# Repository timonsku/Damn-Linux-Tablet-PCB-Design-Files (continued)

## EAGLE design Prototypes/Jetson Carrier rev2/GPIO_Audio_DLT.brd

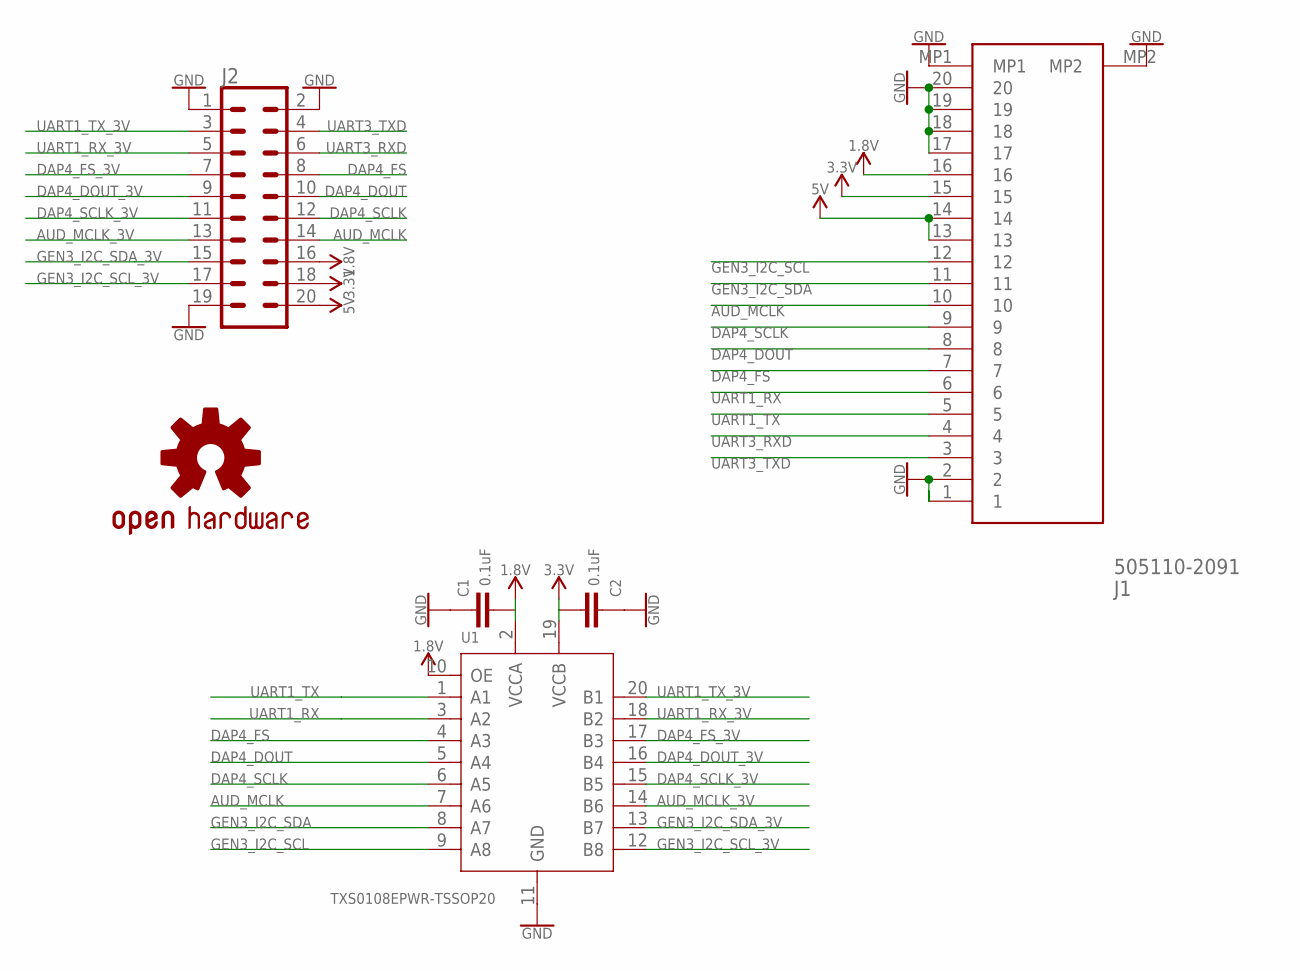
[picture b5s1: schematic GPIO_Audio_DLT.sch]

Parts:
C1, C2: 0.1uF; 0603
J1: 505110-2091; 5051102091
J2: CONN_10X2; 2X10
LOGO1: OSHW-LOGOS-COPPER; OSHW-LOGO-S_COPPER
U1: TXS0108EPWR-TSSOP20; TSSOP20-0.65-6.5X4.4MM

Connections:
1.8V: C1.2, J1.16, J2.16, U1.2 (VCCA), U1.10 (OE)
3.3V: C2.1, J1.15, J2.18, U1.19 (VCCB)
5V: J1.13, J1.14, J2.20
AUD_MCLK: J1.10, J2.14, U1.7 (A6)
AUD_MCLK_3V: J2.13, U1.14 (B6)
DAP4_DOUT: J1.8, J2.10, U1.5 (A4)
DAP4_DOUT_3V: J2.9, U1.16 (B4)
DAP4_FS: J1.7, J2.8, U1.4 (A3)
DAP4_FS_3V: J2.7, U1.17 (B3)
DAP4_SCLK: J1.9, J2.12, U1.6 (A5)
DAP4_SCLK_3V: J2.11, U1.15 (B5)
GEN3_I2C_SCL: J1.12, U1.9 (A8)
GEN3_I2C_SCL_3V: J2.17, U1.12 (B8)
GEN3_I2C_SDA: J1.11, U1.8 (A7)
GEN3_I2C_SDA_3V: J2.15, U1.13 (B7)
GND: C1.1, C2.2, J1.1, J1.2, J1.17, J1.18, J1.19, J1.20, J1.MP1, J1.MP2, J2.1, J2.2, J2.19, U1.11 (GND)
UART1_RX: J1.6, U1.3 (A2)
UART1_RX_3V: J2.5, U1.18 (B2)
UART1_TX: J1.5, U1.1 (A1)
UART1_TX_3V: J2.3, U1.20 (B1)
UART3_RXD: J1.4, J2.6
UART3_TXD: J1.3, J2.4

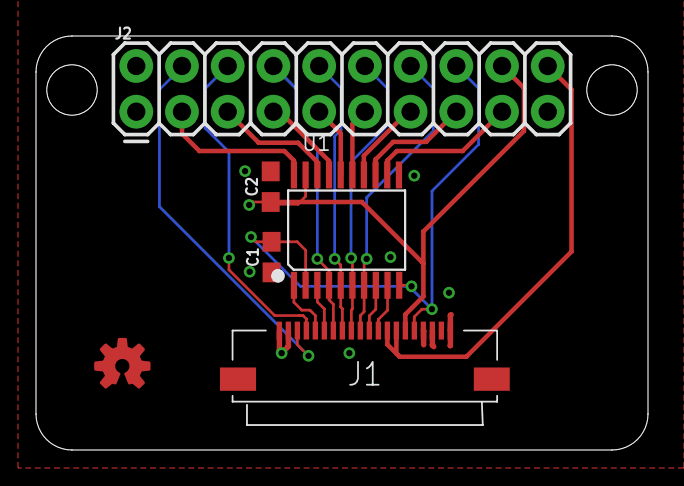
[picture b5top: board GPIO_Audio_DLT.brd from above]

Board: 2 copper layers, 34.0 x 23.0 mm, 6 parts (0 on the bottom side), 22 nets.

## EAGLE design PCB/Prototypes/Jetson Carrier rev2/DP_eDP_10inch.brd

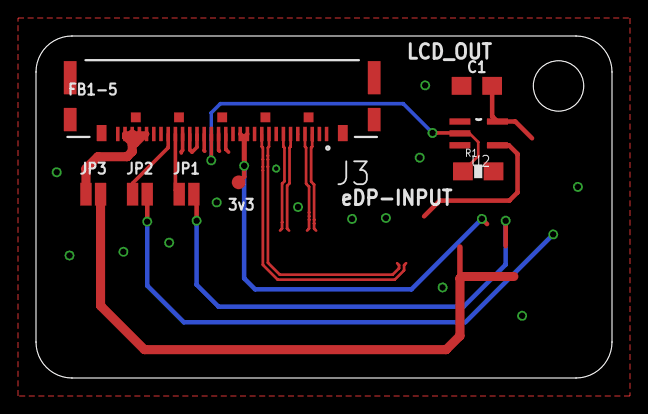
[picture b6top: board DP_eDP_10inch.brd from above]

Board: 4 copper layers, 32.0 x 19.0 mm, 8 parts (0 on the bottom side), 7 nets.

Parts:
C1: 0.1uF; 0603
J3: 20525-030E-2; I-PEX_20525-030E-2
JP1, JP2, JP3: JUMPER-SMT_2_NC_PASTE_NO-SILK; SMT-JUMPER_2_NC_PASTE_NO-SILK
R1: 100k; 0603-RES
TP7: TEST-POINT3; PAD.03X.03
U2: SN74LV1T125DCKR; SOT65P210X110-5N

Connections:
1.8V: C1.2, U2.5
DP_HPD_IN: J3.17, R1.1, U2.2
DP_PWR_3V3: J3.12, J3.13, TP7.P$1
GND: C1.1, J3.2, J3.5, J3.8, J3.11, J3.15, J3.16, J3.18, J3.19, J3.20, J3.21, R1.2, U2.1, U2.3
unnamed: J3.22, JP1.1
unnamed: J3.23, JP2.1
unnamed: J3.26, J3.27, J3.28, J3.29, JP3.1

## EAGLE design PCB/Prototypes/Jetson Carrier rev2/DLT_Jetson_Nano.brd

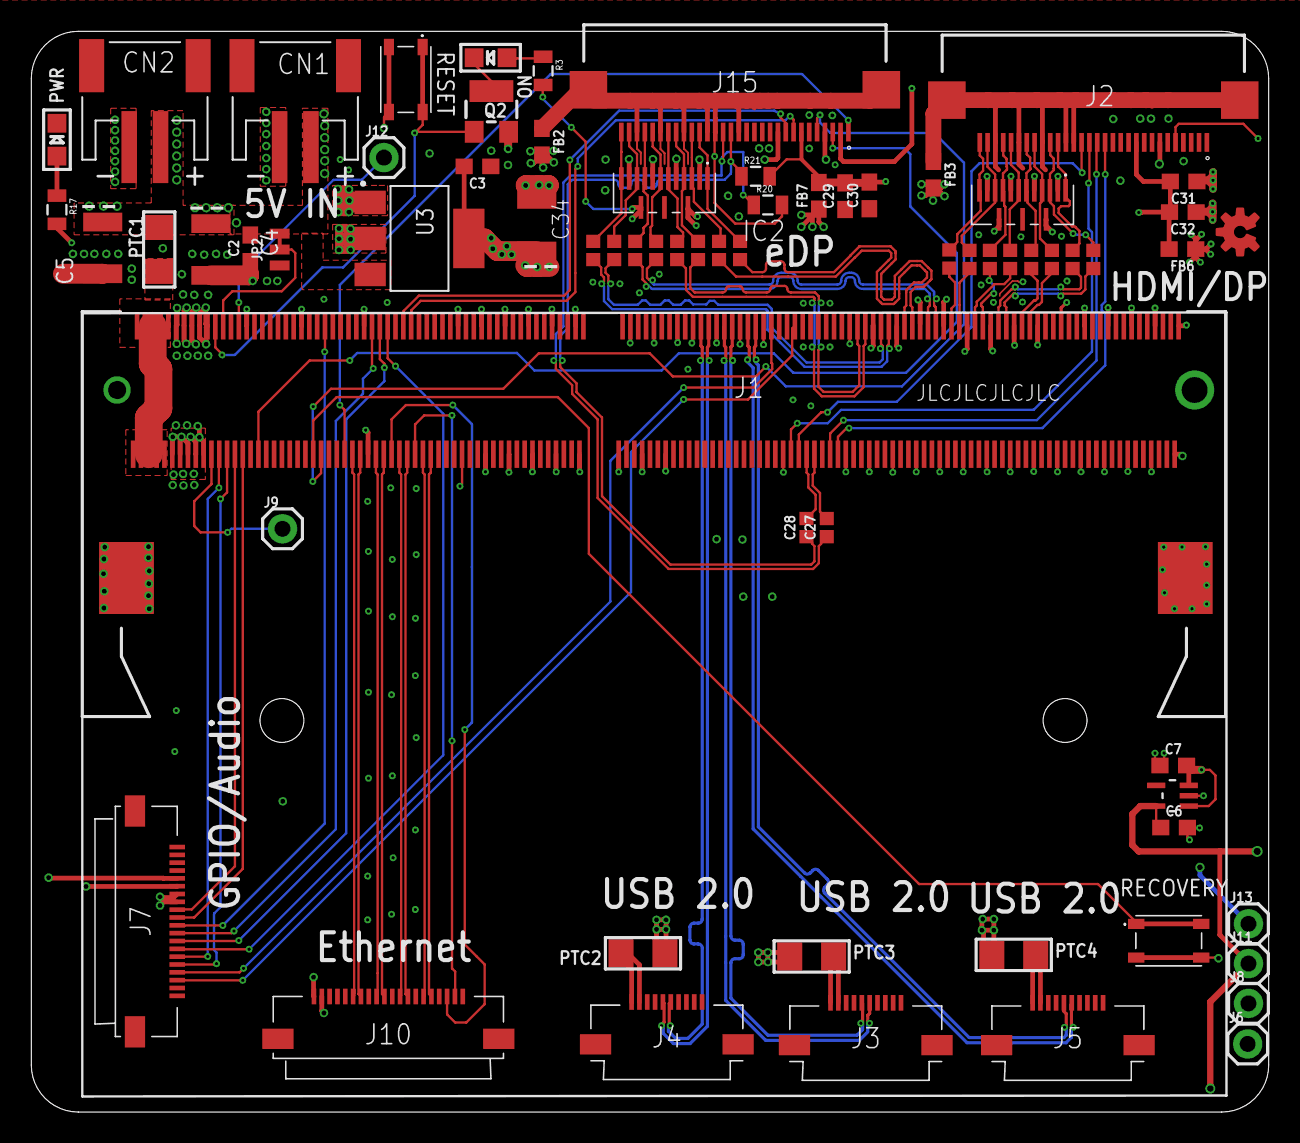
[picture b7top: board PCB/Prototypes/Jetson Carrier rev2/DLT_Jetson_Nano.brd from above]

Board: 4 copper layers, 79.0 x 69.0 mm, 68 parts (0 on the bottom side), 92 nets.

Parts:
C2, C6: 1uF; 0603
C3, C7, C29, C30, C31, C32: 4.7uF; 0603
C4, C5, C34: 47uF; EIA3528
C10, C11, C12, C13, C14, C15, C16, C17, C18, C19, C20, C21, C22, C23, C24, C25, C27, C28: 0.1uF; 0402
CN1, CN2: JST-PH-2-SMT-RA
FB2, FB3, FB6, FB7: .25/3A; 0603
IC1, IC2: TPD8S009DSMR
IC3: TLV70018DCKR; SOT65P210X110-5N
J1: 2309409-1
J2, J15: 54132-3062
J3, J4, J5: 505110-1092; 5051101092
J6, J8, J9, J11, J12, J13: 1X01
J7, J10: 505110-2091; 5051102091
JP2: JUMPER-SMT_3_1-NC_TRACE_NO-SILK; SMT-JUMPER_3_1-NC_TRACE_NO-SILK
LOGO1: OSHW-LOGOS-COPPER; OSHW-LOGO-S_COPPER
ON: CHIPLED_0805
PTC1, PTC2, PTC3, PTC4: 1206
PWR: CHIPLED_0805
Q2: SOT23-W
R3, R17: 0805
R20, R21: 100k; 0805
S2, S4: SKRPADE010
U3: LDL1117S12R; SOT230P700X180-4N

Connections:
1.8V: C6.1, IC3.5, J2.5, J7.5, J11.1, J15.2
3.3V: C3.2, C34.A, FB7.1, J7.6, J8.1, J10.2, R17.2, U3.2, U3.4
5V: C2.2, C4.A, C5.A, C7.2, CN1.1, CN2.1, FB6.1, IC1.13, IC1.15, IC2.13, IC2.15, IC3.1, IC3.3, J7.7, J7.8, J10.1, J13.1, J15.4, J15.10, JP2.3, PTC1.2, PTC2.1, PTC3.1, PTC4.1, R3.2, U3.3
#PWR_BUTTON: J1.240, J9.1
#RECOVERY: J1.214, S4.1, S4.2
#RESET: J1.239, Q2.1, S2.1, S2.2
#SHUTDOWN_REQ: J1.233, J12.1
AUD_MCLK: J1.211, J7.11
DAP4_DOUT: J1.197, J7.13
DAP4_FS: J1.195, J7.14
DAP4_SCLK: J1.199, J7.12
DP_GND: FB2.1, J15.15, J15.18, J15.19, J15.22, J15.25, J15.28, J15.31, J15.32, R20.2
DP_PWR_3V3: C29.2, C30.2, FB7.2, J2.7, J15.7, R21.2
EDP0_TX_C_N: C25.2, IC2.10, J15.29
EDP0_TX_C_P: C24.2, IC2.12, J15.30
EDP0_TX_N: C25.1, J1.77
EDP0_TX_P: C24.1, J1.75
EDP1_TX_C_N: C23.2, IC2.7, J15.26
EDP1_TX_C_P: C22.2, IC2.9, J15.27
EDP1_TX_N: C23.1, J1.63
EDP1_TX_P: C22.1, J1.65
EDP2_TX_C_N: C21.2, IC2.4, J15.23
EDP2_TX_C_P: C20.2, IC2.6, J15.24
EDP2_TX_N: C21.1, J1.83
EDP2_TX_P: C20.1, J1.81
EDP3_TX_C_N: C19.2, IC2.1, J15.20
EDP3_TX_C_P: C18.2, IC2.3, J15.21
EDP3_TX_N: C19.1, J1.69
EDP3_TX_P: C18.1, J1.71
EDP_AUX_C_N: C28.1, J15.16, R21.1
EDP_AUX_C_P: C27.1, J15.17, R20.1
EDP_AUX_N: C28.2, J1.96
EDP_AUX_P: C27.2, J1.94
EDP_HPD: J1.92, J15.14
ENET_LED0: J1.194, J10.18
ENET_LED1: J1.188, J10.19
ENET_TRD0_N: J1.202, J10.7
ENET_TRD0_P: J1.204, J10.6
ENET_TRD1_N: J1.196, J10.10
ENET_TRD1_P: J1.198, J10.9
ENET_TRD2_N: J1.190, J10.13
ENET_TRD2_P: J1.192, J10.12
ENET_TRD3_N: J1.186, J10.15
ENET_TRD3_P: J1.184, J10.16
GEN2_I2C_SCL: J1.189, J15.8
GEN2_I2C_SDA: J1.191, J15.9
GEN3_I2C_SCL: J1.234, J7.9
GEN3_I2C_SDA: J1.232, J7.10
GND: C2.1, C3.1, C4.C, C5.C, C6.2, C7.1, C29.1, C30.1, C31.1, C32.1, C34.C, CN1.2, CN2.2, FB2.2, FB3.2, IC1.2, IC1.5, IC1.8, IC1.11, IC2.2, IC2.5, IC2.8, IC2.11, IC3.2, J1.1, J1.2, J1.7, J1.8, J1.13, J1.14, J1.19, J1.20, J1.25, J1.26, J1.31, J1.32, J1.37, J1.38, J1.43, J1.44, J1.49, J1.50, J1.55, J1.56, J1.61, J1.62, J1.67, J1.68, J1.73, J1.74, J1.79, J1.80, J1.85, J1.86, J1.102, J1.107, J1.113, J1.119, J1.125, J1.129, J1.132, J1.135, J1.138, J1.141, J1.144, J1.146, J1.147, J1.152, J1.153, J1.158, J1.159, J1.164, J1.165, J1.170, J1.171, J1.176, J1.177, J1.200, J1.201, J1.217, J1.231, J1.241, J1.242, J1.243, J1.244, J1.245, J1.246, J1.247, J1.248, J1.249, J1.250, J1.261, J1.262, J1.263, J1.264, J2.6, J2.8, J2.9, J2.11, J2.13, J3.7, J3.8, J3.11, J3.12, J4.7, J4.8, J4.11, J4.12, J5.7, J5.8, J5.11, J5.12, J6.1, J7.1, J7.2, J7.3, J7.4, J7.19, J7.20, J7.MP1, J7.MP2, J10.5, J10.8, J10.11, J10.14, J10.17, J10.MP1, J10.MP2, J15.6, J15.11, J15.12, J15.13, JP2.1, PWR.C, Q2.2, S2.3, S2.4, S4.3, S4.4, U3.1
GPIO13_PE6_PWM: J1.228, J15.3
HDMI_CEC: J1.90, J2.15
HDMI_GND: FB3.1, J2.18, J2.19, J2.22, J2.25, J2.28, J2.31, J2.32
HDMI_HPD: J1.88, J2.14
HDMI_PWR_5V: C31.2, C32.2, FB6.2, J2.10
HDMI_SCL: J1.100, J2.16
HDMI_SDA: J1.98, J2.17
LCD_BL_EN: J1.212, J15.5
LCD_BL_PWM: J1.206, J15.1
unnamed: ON.C, Q2.3
unnamed: ON.A, R3.1
unnamed: PWR.A, R17.1
PWR_EN: J1.237, JP2.2
TMDS_CLK_C_N: C16.2, IC1.1, J2.20
TMDS_CLK_C_P: C17.2, IC1.3, J2.21
TMDS_CLK_N: C16.1, J1.47
TMDS_CLK_P: C17.1, J1.45
TMDS_D0_C_N: C14.2, IC1.4, J2.23
TMDS_D0_C_P: C15.2, IC1.6, J2.24
TMDS_D0_N: C14.1, J1.39
TMDS_D0_P: C15.1, J1.41
TMDS_D1_C_N: C12.2, IC1.7, J2.26
TMDS_D1_C_P: C13.2, IC1.9, J2.27
TMDS_D1_N: C12.1, J1.53
TMDS_D1_P: C13.1, J1.51
TMDS_D2_C1_N: C10.2, IC1.10, J2.29
TMDS_D2_C_P: C11.2, IC1.12, J2.30
TMDS_D2_N: C10.1, J1.57
TMDS_D2_P: C11.1, J1.59
UART1_RX: J1.238, J7.15
UART1_TX: J1.236, J7.16
UART3_RXD: J1.105, J7.17
UART3_TXD: J1.99, J7.18
USB0(OTG)_D_N: J1.109, J5.5
USB0(OTG)_D_P: J1.111, J5.6
USB1_D_N: J1.115, J3.5
USB1_D_P: J1.117, J3.6
USB2_D_N: J1.121, J4.5
USB2_D_P: J1.123, J4.6
VBUS0: J5.1, J5.2, PTC4.2
VBUS1: J3.1, J3.2, PTC3.2
VBUS2: J4.1, J4.2, PTC2.2
VDD: J1.251, J1.252, J1.253, J1.254, J1.255, J1.256, J1.257, J1.258, J1.259, J1.260, PTC1.1

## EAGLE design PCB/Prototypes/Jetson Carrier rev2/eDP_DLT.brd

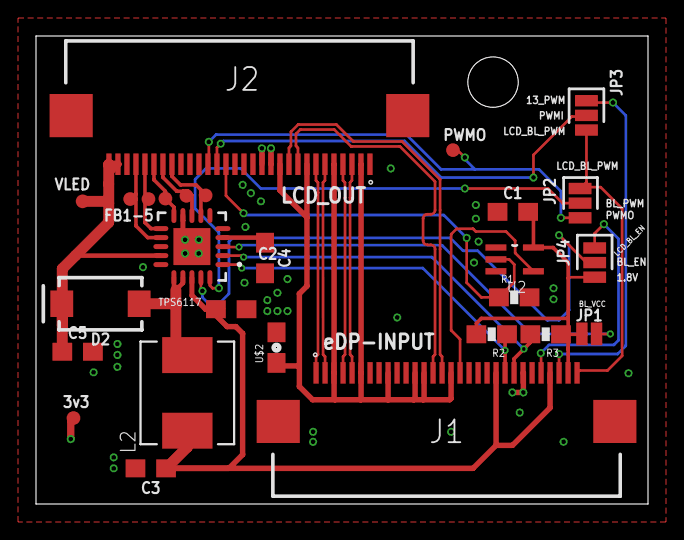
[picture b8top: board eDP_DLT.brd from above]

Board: 4 copper layers, 34.0 x 26.0 mm, 27 parts (0 on the bottom side), 31 nets.

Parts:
C1: 0.1uF; 0603
C2, C5: 4.7uF; 0603
C3, C4: 1.0uF; 0603
D2: 3A/40V/500mV; SMA-DIODE
J1, J2: 54132-3062
JP1: JUMPER-SMT_2_NO_NO-SILK; SMT-JUMPER_2_NO_NO-SILK
JP2, JP3, JP4: JUMPER-SMT_3_1-NC_PASTE_NO-SILK; SMT-JUMPER_3_1-NC_PASTE_NO-SILK
L2: SRP5020TA-4R7M; IND_SRP5020TA-4R7M
R1: 100k; 0603-RES
R2, R3: 10k; 0603-RES
TP1, TP2, TP3, TP4, TP5, TP6, TP7, TP8: TEST-POINT3; PAD.03X.03
TPS6117: TPS61177ARGRR; RGR0020A
U2: SN74LV1T125DCKR; SOT65P210X110-5N
U$2: FB; 0603

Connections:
1.8V: C1.2, J1.29, JP1.1, JP4.1, R2.2, R3.1, U2.5
5V: C2.1, C3.1, J1.21, J1.27, L2.1, TPS6117.18
BL_EN: JP4.2, TPS6117.19
BL_PWM: JP2.2, TPS6117.20
DP_GND: J1.3, J1.6, J1.9, J1.12, J1.13, J1.16, J2.2, J2.5, J2.8, J2.11, U$2.1
DP_HPD_IN: J2.17, R1.1, U2.2
DP_PWR_3V3: J1.24, J2.12, J2.13, TP7.P$1
EDP0_TX_C_N: J1.2, J2.6
EDP0_TX_C_P: J1.1, J2.7
EDP1_TX_C_N: J1.5, J2.3
EDP1_TX_C_P: J1.4, J2.4
EDP_AUX_N: J1.15, J2.10
EDP_AUX_P: J1.14, J2.9
EDP_HPD: J1.17, U2.4
FB1: J2.27, TP1.P$1, TPS6117.12
FB2: J2.26, TP2.P$1, TPS6117.11
FB3: J2.25, TP3.P$1, TPS6117.10
FB4: J2.24, TP4.P$1, TPS6117.8
FB5: J2.23, TP5.P$1, TPS6117.7
GEN2_I2C_SCL: J1.23, R3.2, TPS6117.2
GEN2_I2C_SDA: J1.22, R2.1, TPS6117.1
GND: C1.1, C2.2, C3.2, C4.2, C5.2, J1.18, J1.19, J1.20, J1.25, J1.31, J1.32, J2.15, J2.16, J2.31, J2.32, R1.2, TPS6117.5, TPS6117.6, TPS6117.9, TPS6117.15, TPS6117.21, U2.1, U2.3, U$2.2
GPIO13_PE6_PWM: J1.28, JP3.3
LCD_BL_EN: J1.26, JP4.3
LCD_BL_PWM: J1.30, JP2.3, JP3.1
LXB: D2.A, L2.2, TPS6117.16, TPS6117.17
unnamed: JP1.2, TPS6117.3
unnamed: C4.1, TPS6117.4
PWMI: J2.18, JP3.2
PWMO: J2.19, JP2.1, TP8.P$1
VLED: C5.1, D2.C, J2.29, J2.30, TP6.P$1, TPS6117.14

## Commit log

2019-09-30 added mechanical files
2019-10-01 clean up of rev.2 PCB files
